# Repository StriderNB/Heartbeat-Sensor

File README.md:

# Heartbeat-Sensor

An MW2 Inspired heartbeat sensor

# Features

*(Eventually) Track up to 3 targets simultaneously

Detects distance and velocity of targets

Seamless tracking and screen refreshing

Can be powered by usb-c port or rechargeable battery

Brightness control

# Main Hardware
XIAO-ESP32-S3

24G HLK-LD2450 Radar Sensor

ST7789V 2.8 Inch SPI Display

Rechargeable 3.7V LiPo Battery

# Wiring
All connections are visible in image of schematic at bottom of page. It's currently designed to be wired by hand, but can be easily adapted to fit on a pcb.

# Software
Requires TFT_eSPI.h by Bodmer and SPI.h libraries

# Code
Still in progress and untested. Although it should be the bare minimum to get the project working.

# BOM
| Item | Qty | Supplier | Cost/item | Total Cost | Link |
| :--- | :---: | :--- | :---: | :---: | :--- |
| XIAO-ESP32-S2 | 1 | Aliexpress | $9.63 | $9.63 | [Link](https://www.aliexpress.us/item/3256806801590776.html?spm=a2g0o.cart.0.0.541338da47ZNNX&mp=1&pdp_npi=6%40dis%21USD%21USD+56.03%21USD+9.63%21%21USD+9.63%21%21%21%40210311c217935924233951417e0ef1%2112000056625194548%21ct%21US%218321405938%21%211%210%21&_gl=1*qjvvj7*_gcl_aw*R0NMLjE3OTM0Njg0NzEuQ2p3S0NBandvNWJYQmhBRUVpd0FrZ3BnWEJoUkpkZlh0UVZka2ZmbUI5T204eENyeVA5OFlobmhhVWVjYlFVcWRmaWFiNW9QbjdGQTBSb0NnMThRQXZEX0J3RQ..*_gcl_dc*R0NMLjE3OTM0Njg0NzEuQ2p3S0NBandvNWJYQmhBRUVpd0FrZ3BnWEJoUkpkZlh0UVZka2ZmbUI5T204eENyeVA5OFlobmhhVWVjYlFVcWRmaWFiNW9QbjdGQTBSb0NnMThRQXZEX0J3RQ..*_gcl_au*MjEyNDg5MTc2NC4xNzkwNTM4MDQ3*_ga*NzA2MzgzNDcwLjE3OTMxNDk0MDY.*_ga_VED1YSGNC7*czE3OTM1OTA4ODIkbzE2JGcxJHQxNzkzNTkyMzA4JGoxNCRsMCRoMA..&gatewayAdapt=glo2usa) |
| 35mm 20k Potentiometer Slider | 1 | AliExpress | $2.96 | $2.96 | [Link](https://www.aliexpress.us/item/3256808527031041.html?spm=a2g0o.cart.0.0.6eb838daCB40T6&mp=1&pdp_npi=6%40dis%21USD%21USD+3.00%21USD+2.75%21%21USD+2.75%21%21%21%40210311c217935923455405476e0ef1%2112000046545295125%21ct%21US%218321405938%21%212%210%21&_gl=1*1s7wowk*_gcl_aw*R0NMLjE3OTM0Njg0NzEuQ2p3S0NBandvNWJYQmhBRUVpd0FrZ3BnWEJoUkpkZlh0UVZka2ZmbUI5T204eENyeVA5OFlobmhhVWVjYlFVcWRmaWFiNW9QbjdGQTBSb0NnMThRQXZEX0J3RQ..*_gcl_dc*R0NMLjE3OTM0Njg0NzEuQ2p3S0NBandvNWJYQmhBRUVpd0FrZ3BnWEJoUkpkZlh0UVZka2ZmbUI5T204eENyeVA5OFlobmhhVWVjYlFVcWRmaWFiNW9QbjdGQTBSb0NnMThRQXZEX0J3RQ..*_gcl_au*MjEyNDg5MTc2NC4xNzkwNTM4MDQ3*_ga*NzA2MzgzNDcwLjE3OTMxNDk0MDY.*_ga_VED1YSGNC7*czE3OTM1OTA4ODIkbzE2JGcxJHQxNzkzNTkyMjI4JGozNCRsMCRoMA..&gatewayAdapt=glo2usa) |
| 24G HLK-LD2450 | 1 | AliExpress | $6.15 | $6.15 | [Link](https://www.aliexpress.us/item/3256805935608347.html?spm=a2g0o.cart.0.0.597738da8YWaIu&mp=1&pdp_npi=6%40dis%21USD%21USD+6.15%21USD+1.09%21%21USD+1.09%21%21%21%40210311c217935922787962724e0ef1%2112000035851121206%21ct%21US%218321405938%21%211%210%21&_gl=1*p4p9qr*_gcl_aw*R0NMLjE3OTM0Njg0NzEuQ2p3S0NBandvNWJYQmhBRUVpd0FrZ3BnWEJoUkpkZlh0UVZka2ZmbUI5T204eENyeVA5OFlobmhhVWVjYlFVcWRmaWFiNW9QbjdGQTBSb0NnMThRQXZEX0J3RQ..*_gcl_dc*R0NMLjE3OTM0Njg0NzEuQ2p3S0NBandvNWJYQmhBRUVpd0FrZ3BnWEJoUkpkZlh0UVZka2ZmbUI5T204eENyeVA5OFlobmhhVWVjYlFVcWRmaWFiNW9QbjdGQTBSb0NnMThRQXZEX0J3RQ..*_gcl_au*MjEyNDg5MTc2NC4xNzkwNTM4MDQ3*_ga*NzA2MzgzNDcwLjE3OTMxNDk0MDY.*_ga_VED1YSGNC7*czE3OTM1OTA4ODIkbzE2JGcxJHQxNzkzNTkyMTY0JGozNiRsMCRoMA..&gatewayAdapt=glo2usa) |
| 3.7V LiPo Battery | 1 | AliExpress | $4.75 | $4.75 | [Link](https://www.aliexpress.us/item/3256808033130350.html?spm=a2g0o.cart.0.0.345338dah4GBOJ&mp=1&pdp_npi=6%40dis%21USD%21USD+11.32%21USD+5.66%21%21USD+5.66%21%21%21%402101de2517934123247658089e1099%2112000044276127880%21ct%21US%218321405938%21%211%210%21&_gl=1*1trtvm4*_gcl_aw*R0NMLjE3OTM0MTIyMTMuQ2p3S0NBandnSkhYQmhCR0Vpd0FIb2hKcXhsWXZpOWpkaXdQaUxUQnpMbGxGVE14SVpLNHJvN2dXUmZEeFFQelQ3NVBFeGgtOU9ZSUVCb0NRSUFRQXZEX0J3RQ..*_gcl_dc*R0NMLjE3OTM0MTIyMTMuQ2p3S0NBandnSkhYQmhCR0Vpd0FIb2hKcXhsWXZpOWpkaXdQaUxUQnpMbGxGVE14SVpLNHJvN2dXUmZEeFFQelQ3NVBFeGgtOU9ZSUVCb0NRSUFRQXZEX0J3RQ..*_gcl_au*MjEyNDg5MTc2NC4xNzkwNTM4MDQ3*_ga*NzA2MzgzNDcwLjE3OTMxNDk0MDY.*_ga_VED1YSGNC7*czE3OTM0MTE5NzkkbzEwJGcxJHQxNzkzNDEyMjEyJGo1OCRsMCRoMA..&gatewayAdapt=glo2usa) |
| ST7789V 2.8 Inch SPI Serial Display | 1 | AliExpress | $5.76 | $5.76 | [Link](https://www.aliexpress.us/item/3256804371601818.html?spm=a2g0o.cart.0.0.597738daurL5Pt&mp=1&pdp_npi=6%40dis%21USD%21USD+5.76%21USD+2.76%21%21USD+2.76%21%21%21%402101de2517933075277234216e0f4f%2112000056542446061%21ct%21US%218321405938%21%211%210%21&_gl=1*2rb8zi*_gcl_aw*R0NMLjE3OTMzMDczOTQuQ2p3S0NBandsNEhYQmhBakVpd0FIbHBXaEdldGdTaDRVVXMtYVE1ckwyaFpTQkIzNkZNXzEzUXJQS1F4bFhMVDBMbHVxaWNhRUtTbG9Cb0NEY2dRQXZEX0J3RQ..*_gcl_dc*R0NMLjE3OTMzMDczOTQuQ2p3S0NBandsNEhYQmhBakVpd0FIbHBXaEdldGdTaDRVVXMtYVE1ckwyaFpTQkIzNkZNXzEzUXJQS1F4bFhMVDBMbHVxaWNhRUtTbG9Cb0NEY2dRQXZEX0J3RQ..*_gcl_au*MjEyNDg5MTc2NC4xNzkwNTM4MDQ3*_ga*NzA2MzgzNDcwLjE3OTMxNDk0MDY.*_ga_VED1YSGNC7*czE3OTMzMDcxODIkbzgkZzEkdDE3OTMzMDc0MTckajUwJGwwJGgw&gatewayAdapt=glo2usa) |
| 5V DC-DC Step-Up Power Module | 1 | AliExpress | $2.83 | $2.83 | [Link](https://www.aliexpress.us/item/3256805438663158.html?spm=a2g0o.cart.0.0.597738daurL5Pt&mp=1&pdp_npi=6%40dis%21USD%21USD+2.83%21USD+1.09%21%21USD+1.09%21%21%21%402101de2517933075277234216e0f4f%2112000043421985868%21ct%21US%218321405938%21%211%210%21&_gl=1*1nhnar5*_gcl_aw*R0NMLjE3OTMzMDczOTQuQ2p3S0NBandsNEhYQmhBakVpd0FIbHBXaEdldGdTaDRVVXMtYVE1ckwyaFpTQkIzNkZNXzEzUXJQS1F4bFhMVDBMbHVxaWNhRUtTbG9Cb0NEY2dRQXZEX0J3RQ..*_gcl_dc*R0NMLjE3OTMzMDczOTQuQ2p3S0NBandsNEhYQmhBakVpd0FIbHBXaEdldGdTaDRVVXMtYVE1ckwyaFpTQkIzNkZNXzEzUXJQS1F4bFhMVDBMbHVxaWNhRUtTbG9Cb0NEY2dRQXZEX0J3RQ..*_gcl_au*MjEyNDg5MTc2NC4xNzkwNTM4MDQ3*_ga*NzA2MzgzNDcwLjE3OTMxNDk0MDY.*_ga_VED1YSGNC7*czE3OTMzMDcxODIkbzgkZzEkdDE3OTMzMDc4NjIkajU4JGwwJGgw&gatewayAdapt=glo2usa) |
| 50V 10uF Capacitor | 40 | AliExpress | $0.02 | $2.89 | [Link](https://www.aliexpress.us/item/3256811445656016.html?spm=a2g0o.cart.0.0.7ede38daeO72gH&mp=1&pdp_npi=6%40dis%21USD%21USD+2.88%21USD+1.09%21%21USD+1.09%21%21%21%402101e5ab17933132983857097e0ffd%2112000056427936765%21ct%21US%218321405938%21%211%210%21&_gl=1*6ewfz2*_gcl_aw*R0NMLjE3OTMzMTIxODIuQ2owS0NRanczWXZYQmhDREFSSXNBS0Itb3gtMmxIRjZYUWRQeG90UnAydFlFdEZseXA2OU1EdXl5RUlyVDJDUl81eWJKV2prc1FOdFlSMGFBbFVBRUFMd193Y0I.*_gcl_dc*R0NMLjE3OTMzMTIxODIuQ2owS0NRanczWXZYQmhDREFSSXNBS0Itb3gtMmxIRjZYUWRQeG90UnAydFlFdEZseXA2OU1EdXl5RUlyVDJDUl81eWJKV2prc1FOdFlSMGFBbFVBRUFMd193Y0I.*_gcl_au*MjEyNDg5MTc2NC4xNzkwNTM4MDQ3*_ga*NzA2MzgzNDcwLjE3OTMxNDk0MDY.*_ga_VED1YSGNC7*czE3OTMzMDcxODIkbzgkZzEkdDE3OTMzMTMxOTckajQ3JGwwJGgw&gatewayAdapt=glo2usa) |
| 50V 100nF Capacitor | 100 | AliExpress | $0.02 | $2.15 | [Link](https://www.aliexpress.us/item/3256804202811504.html?spm=a2g0o.productlist.main.47.1c4e74c0l1XThG&algo_pvid=dd10d1d4-cb49-45f4-acef-9f18dc0db9b3&algo_exp_id=dd10d1d4-cb49-45f4-acef-9f18dc0db9b3-46&pdp_ext_f=%7B%22order%22%3A%22468%22%2C%22eval%22%3A%221%22%2C%22fromPage%22%3A%22search%22%7D&pdp_npi=6%40dis%21USD%212.15%211.09%21%21%212.15%211.09%21%402103081117933129342097930e0ce6%2112000029007429977%21sea%21US%218321405938%21ABX%211%210%21n_tag%3A-29910%3Bd%3Ad88495b%3Bm03_new_user%3A-29895%3BpisId%3A5000000218165391&curPageLogUid=N2nd954ygKKL&utparam-url=scene%3Asearch%7Cquery_from%3A%7Cx_object_id%3A1005004389126256%7C_p_origin_prod%3A) |
| SPDT Toggle Switch | 20 | PCBWay | $0.10 | $2.04 | [Link](https://www.aliexpress.us/item/3256809760123375.html?spm=a2g0o.cart.0.0.7ede38daeO72gH&mp=1&pdp_npi=6%40dis%21USD%21USD+2.04%21USD+1.09%21%21USD+1.09%21%21%21%402101e5ab17933132983857097e0ffd%2112000050651923109%21ct%21US%218321405938%21%211%210%21&_gl=1*p4s25n*_gcl_aw*R0NMLjE3OTMzMTIxODIuQ2owS0NRanczWXZYQmhDREFSSXNBS0Itb3gtMmxIRjZYUWRQeG90UnAydFlFdEZseXA2OU1EdXl5RUlyVDJDUl81eWJKV2prc1FOdFlSMGFBbFVBRUFMd193Y0I.*_gcl_dc*R0NMLjE3OTMzMTIxODIuQ2owS0NRanczWXZYQmhDREFSSXNBS0Itb3gtMmxIRjZYUWRQeG90UnAydFlFdEZseXA2OU1EdXl5RUlyVDJDUl81eWJKV2prc1FOdFlSMGFBbFVBRUFMd193Y0I.*_gcl_au*MjEyNDg5MTc2NC4xNzkwNTM4MDQ3*_ga*NzA2MzgzNDcwLjE3OTMxNDk0MDY.*_ga_VED1YSGNC7*czE3OTMzMDcxODIkbzgkZzEkdDE3OTMzMTMxODckajU3JGwwJGgw&gatewayAdapt=glo2usa) |
| Estimated total shipping | 1 | | | $9.83 | |
| TOTAL  |  | | | $47.87 | |

# Images

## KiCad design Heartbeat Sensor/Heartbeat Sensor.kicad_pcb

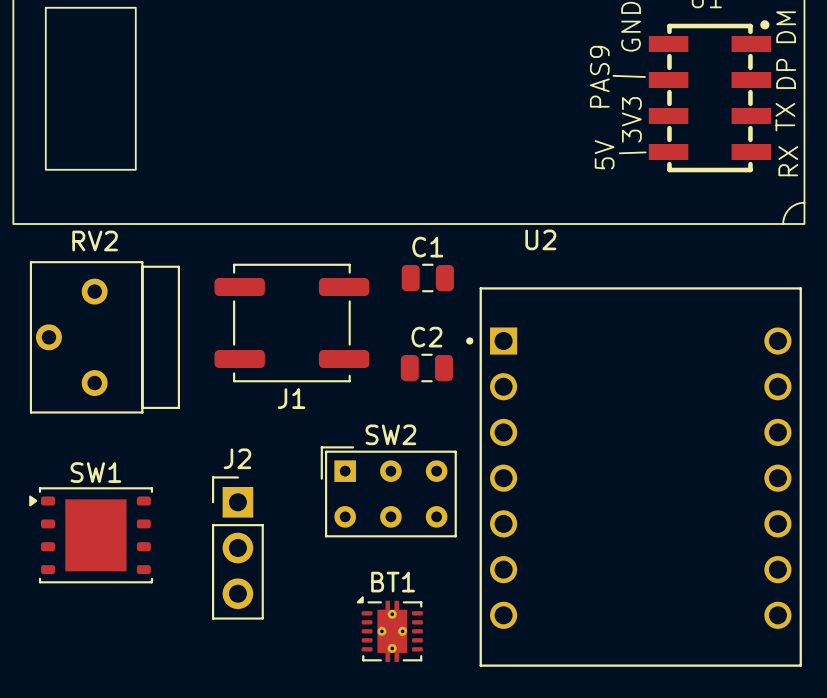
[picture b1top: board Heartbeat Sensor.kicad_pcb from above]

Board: 2 copper layers, 10 parts (0 on the bottom side), 7 nets, no tracks yet.

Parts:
BT1: Battery_Cell; Texas_DRC0010J_ThermalVias
C1: 10µF; C_0805_2012Metric
C2: 100nF; C_0805_2012Metric
J1: Conn_01x08; SW_Push_1P1T_NO_CK_KSC6xxJ
J2: Step_up_Regulator_+5V; PinHeader_1x03_P2.54mm_Vertical
RV2: R_Potentiometer_MountingPin; Potentiometer_Bourns_3339S_Horizontal
SW1: SW_SPDT; WSON-8-1EP_6x5mm_P1.27mm_EP3.4x4mm
SW2: SW_Push; SW_NKK_GW12LJP
U1: ld2450
U2: XIAO-ESP32-S3; XIAO ESP32-S3

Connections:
+3V3: C1.2, C2.2, J1.1, RV2.1, U2.12 (3V3)
+5V: J2.1, U1.5 (5V), U2.14 (5V)
-BATT: BT1.2 (-), C1.1, C2.1, J1.2, J2.2, RV2.3, SW2.1, U1.8 (GND), U2.13 (GND)
/E53_RX: U1.4 (RX), U2.7 (D6/GPIO43)
/E54_TX: U1.3 (TX), U2.8 (D7/GPIO44)
/GPIO4: RV2.2, SW2.2, U2.4 (D3/GPIO4)
unnamed: BT1.1 (+), SW1.2 (B)
